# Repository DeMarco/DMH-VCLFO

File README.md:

# DMH-VCLFO
Kosmo format Voltage Controlled tripple LFO module

## Features
6 waveforms, all +5V/-5V
  - Square
  - Saw
  - Ramp
  - Random
  - Sine
  - Triangle

3 frequency ranges
  - Fast
  - Super Fast (Audio rate!)
  - Slow

Hard Sync input

Can also do VCO duties!

Excellent V/Oct trackig over 5 octaves

CV Amount knob serves as Fine Frequency Adjustment when no cable is connected to CV input

Adjustable range for Fine knob

## Current consumption:
+12V --> 65mA

-12V --> 60mA

## Dimensions
Height: 20cm

Width: 10cm

Depth: 10cm

## PCB set
- Panel
- Controls
- Main
- Submodule (x3)

Final Gerbers available in "Gerbers" folder

## Single VCLFO version
The KiCad project named "Single Unit" contains the circuit for one VCLFO in a single page schematic without any inter-PCB connectors. This can be useful if anyone is interested in designing their own PCBs or entire modules in non-Kosmo dimensions.

## Font
For viewing/customizing in KiCad, I recommend downloading and installing the Nulshock font from Typodermic: https://typodermicfonts.com/nulshock/

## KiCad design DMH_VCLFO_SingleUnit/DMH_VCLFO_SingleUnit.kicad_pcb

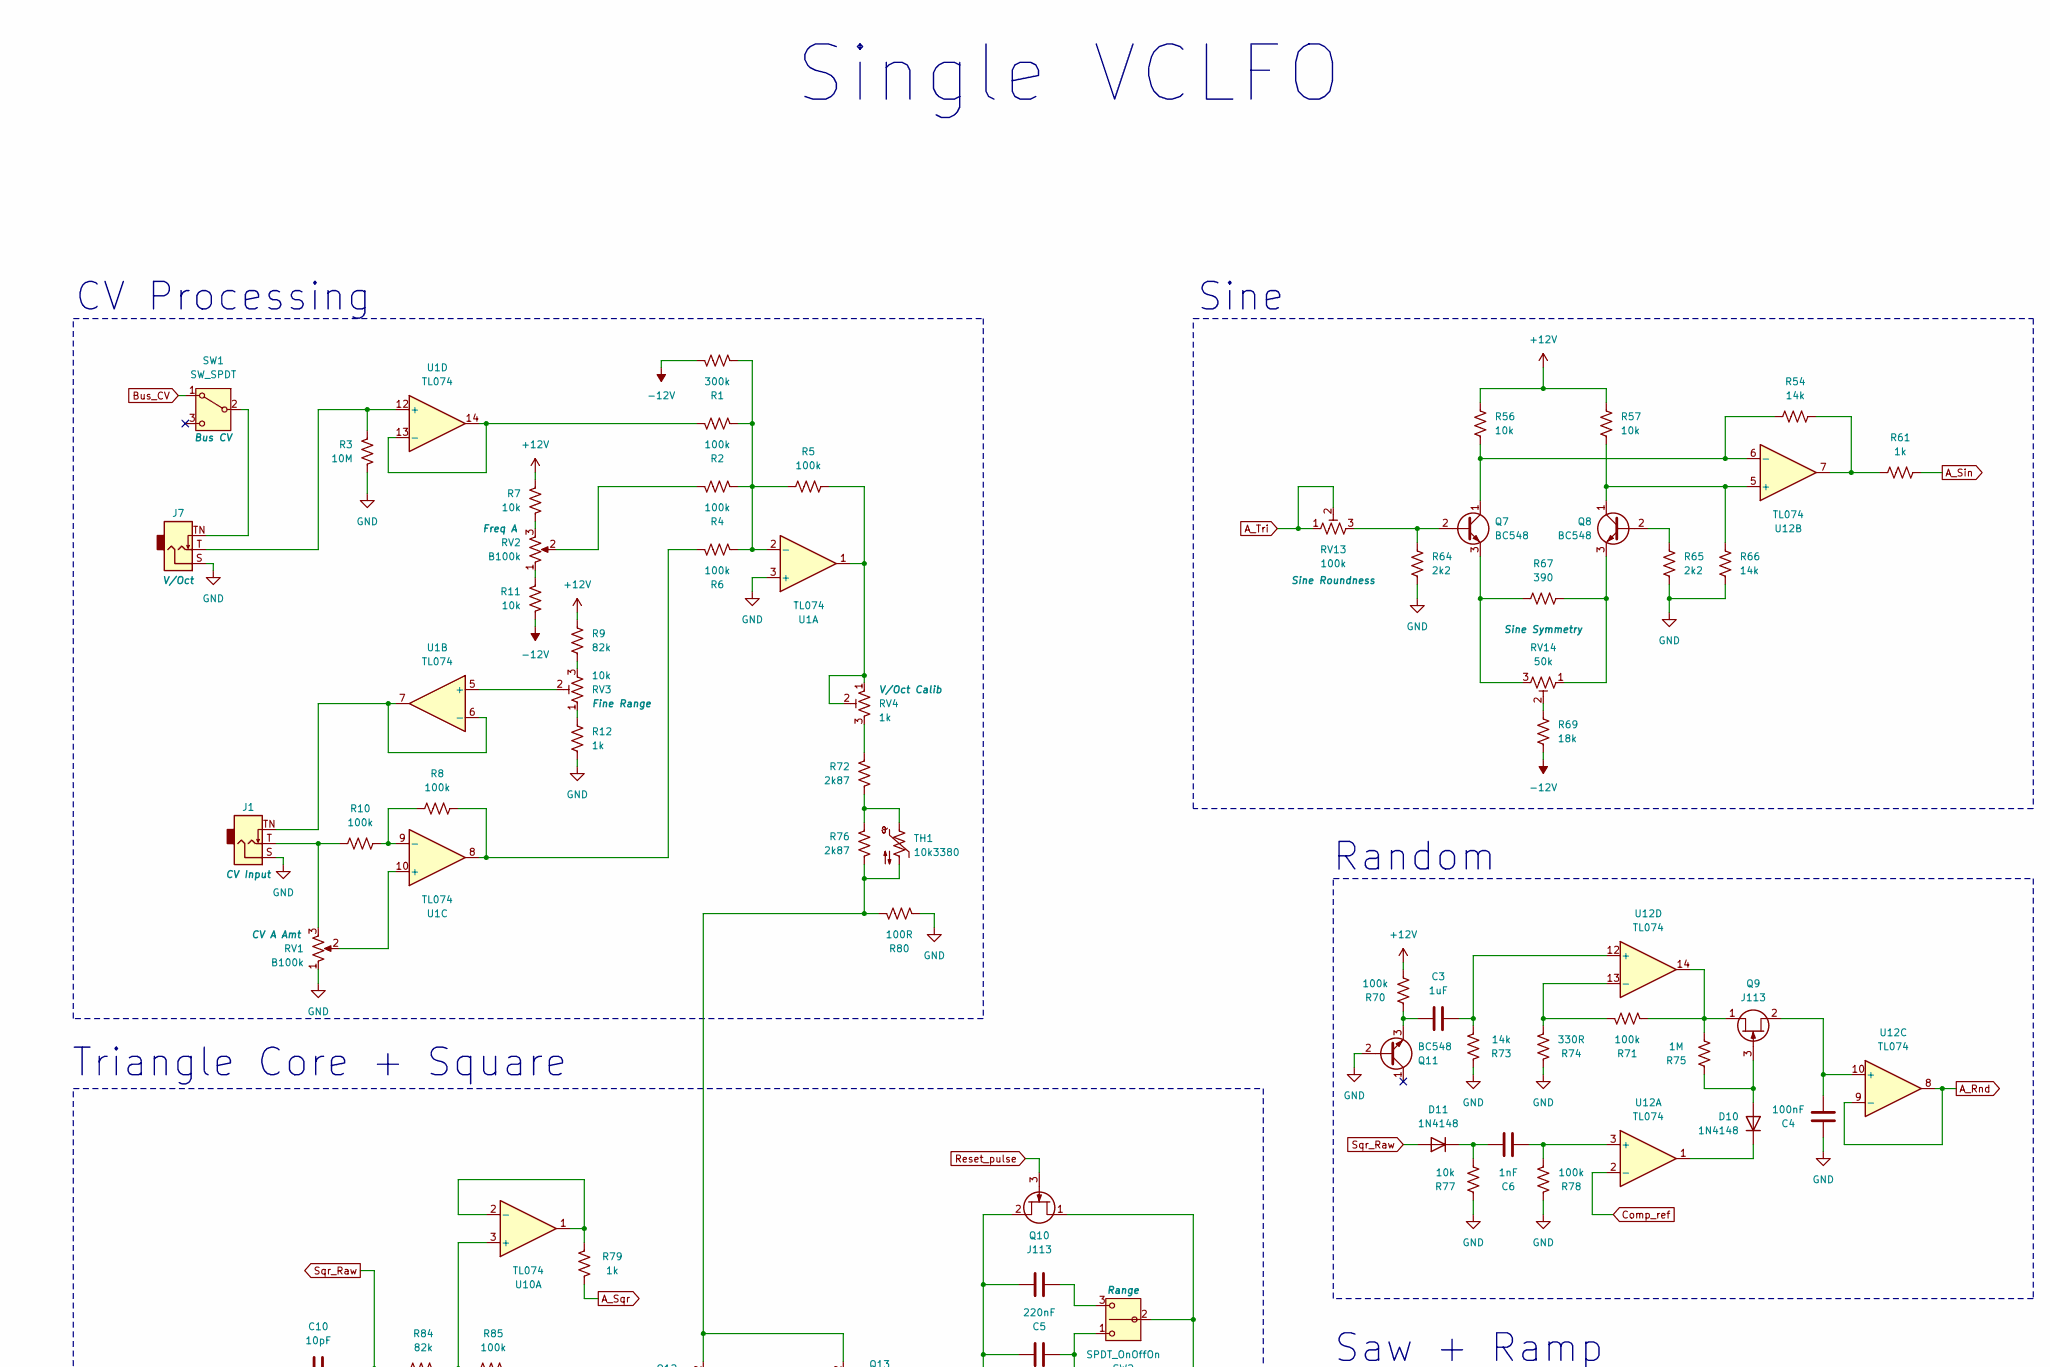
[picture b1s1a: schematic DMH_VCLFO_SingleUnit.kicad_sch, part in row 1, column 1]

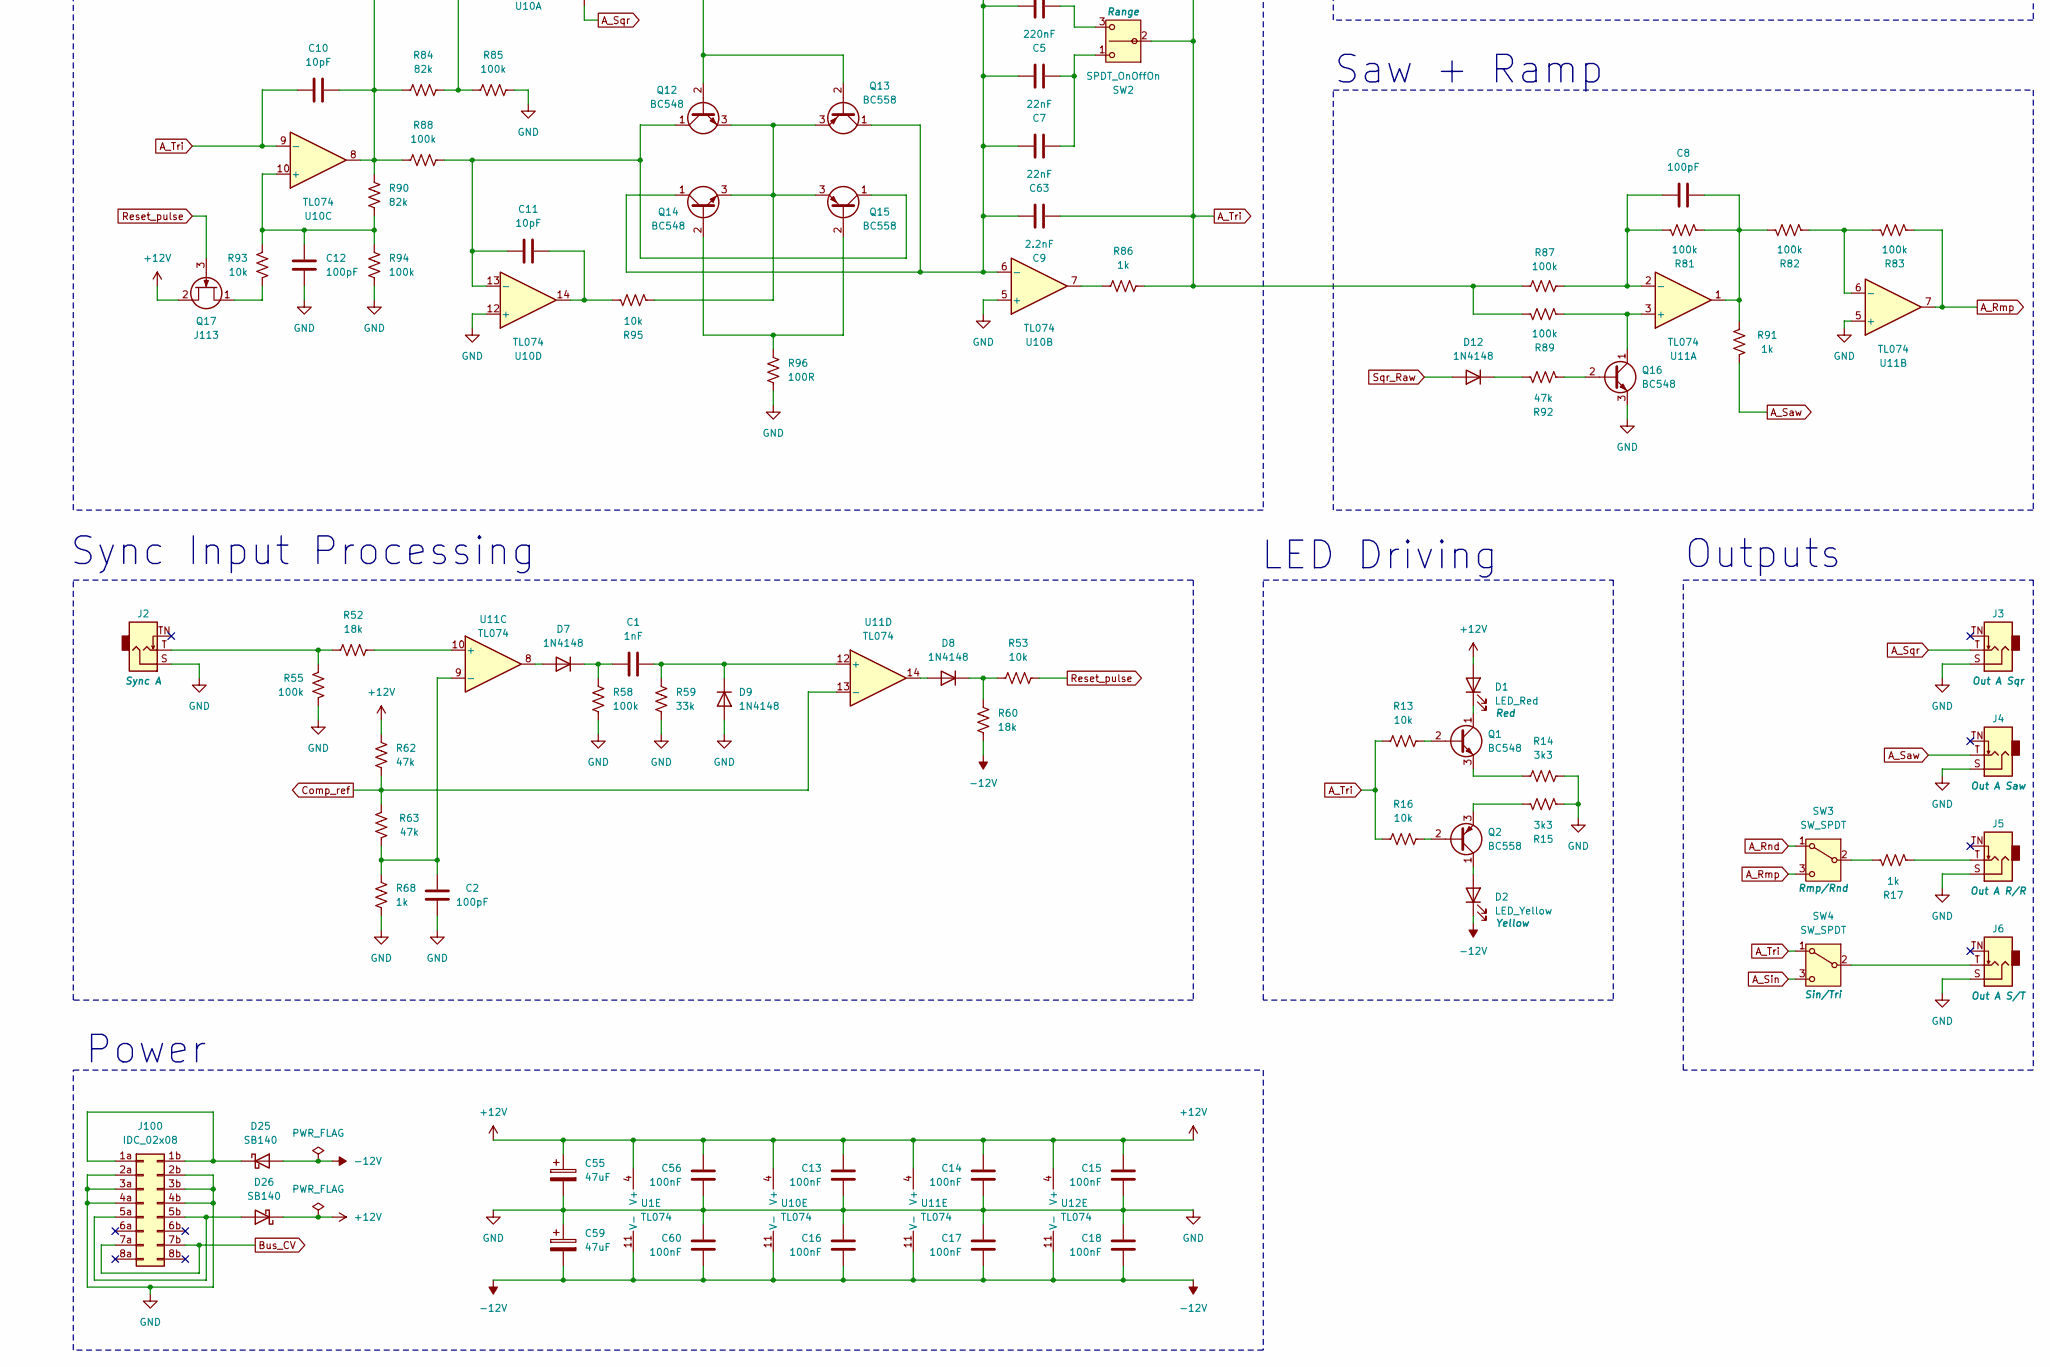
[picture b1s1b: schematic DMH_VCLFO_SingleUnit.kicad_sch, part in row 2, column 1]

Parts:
C1, C6: 1nF; C_Disc_D4.3mm_W1.9mm_P5.00mm
C2, C8, C12: 100pF; C_Disc_D3.0mm_W2.0mm_P2.50mm
C3: 1uF; C_Disc_D4.3mm_W1.9mm_P5.00mm
C4, C13, C14, C15, C16, C17, C18, C56, C60: 100nF; C_Disc_D4.3mm_W1.9mm_P5.00mm
C5: 220nF; C_Disc_D4.3mm_W1.9mm_P5.00mm
C7, C63: 22nF; C_Disc_D4.3mm_W1.9mm_P5.00mm
C9: 2.2nF; C_Disc_D3.0mm_W2.0mm_P2.50mm
C10, C11: 10pF; C_Disc_D3.0mm_W2.0mm_P2.50mm
C55, C59: 47uF; CP_Radial_D5.0mm_P2.00mm
D1: LED_Red; LED_D3.0mm
D2: LED_Yellow; LED_D3.0mm
D7, D8, D9, D10, D11, D12: 1N4148; D_DO-35_SOD27_P7.62mm_Horizontal
D25, D26: SB140; D_DO-41_SOD81_P10.16mm_Horizontal
J1, J2, J3, J4, J5, J6, J7: TS_Jack_6.35mm_Sw; CUI_MJ-63052A
J100: IDC_02x08; IDC-Header_2x08_P2.54mm_Vertical_Eurorack
Q1, Q7, Q8, Q11, Q12, Q14, Q16: BC548; TO-92L_Inline_Wide
Q2, Q13, Q15: BC558; TO-92L_Inline_Wide
Q9, Q10, Q17: J113; TO-92L_Inline
R1: 300k; R_Axial_DIN0207_L6.3mm_D2.5mm_P7.62mm_Horizontal
R2, R4, R5, R6, R8, R10, R55, R58, R70, R71, R78, R81, R82, R83, R85, R87, R88, R89, R94: 100k; R_Axial_DIN0207_L6.3mm_D2.5mm_P7.62mm_Horizontal
R3: 10M; R_Axial_DIN0207_L6.3mm_D2.5mm_P7.62mm_Horizontal
R7, R11, R13, R16, R53, R56, R57, R77, R93, R95: 10k; R_Axial_DIN0207_L6.3mm_D2.5mm_P7.62mm_Horizontal
R9, R84, R90: 82k; R_Axial_DIN0207_L6.3mm_D2.5mm_P7.62mm_Horizontal
R12, R17, R61, R68, R79, R86, R91: 1k; R_Axial_DIN0207_L6.3mm_D2.5mm_P7.62mm_Horizontal
R14, R15: 3k3; R_Axial_DIN0207_L6.3mm_D2.5mm_P7.62mm_Horizontal
R52, R60, R69: 18k; R_Axial_DIN0207_L6.3mm_D2.5mm_P7.62mm_Horizontal
R54, R66, R73: 14k; R_Axial_DIN0207_L6.3mm_D2.5mm_P7.62mm_Horizontal
R59: 33k; R_Axial_DIN0207_L6.3mm_D2.5mm_P7.62mm_Horizontal
R62, R63, R92: 47k; R_Axial_DIN0207_L6.3mm_D2.5mm_P7.62mm_Horizontal
R64, R65: 2k2; R_Axial_DIN0207_L6.3mm_D2.5mm_P7.62mm_Horizontal
R67: 390; R_Axial_DIN0207_L6.3mm_D2.5mm_P7.62mm_Horizontal
R72, R76: 2k87; R_Axial_DIN0207_L6.3mm_D2.5mm_P7.62mm_Horizontal
R74: 330R; R_Axial_DIN0207_L6.3mm_D2.5mm_P7.62mm_Horizontal
R75: 1M; R_Axial_DIN0207_L6.3mm_D2.5mm_P7.62mm_Horizontal
R80, R96: 100R; R_Axial_DIN0207_L6.3mm_D2.5mm_P7.62mm_Horizontal
RV1, RV2: B100k; Potentiometer_Alpha_RD901F-40-00D_Single_Vertical
RV3: 10k; Potentiometer_Bourns_3296W_Vertical
RV4: 1k; Potentiometer_Bourns_3296W_Vertical
RV13: 100k; Potentiometer_Bourns_3296W_Vertical
RV14: 50k; Potentiometer_Bourns_3296W_Vertical
SW1, SW3, SW4: SW_SPDT; Toggle_Switch_TE
SW2: SPDT_OnOffOn; Toggle_Switch_TE
TH1: 10k3380; R_Axial_DIN0204_L3.6mm_D1.6mm_P1.90mm_Vertical
U1, U10, U11, U12: TL074; DIP-14_W7.62mm_Socket

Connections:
+12V: C13.1, C14.1, C15.1, C55.1, C56.1, D1.2 (A), D26.1 (K), Q17.2 (S), R7.1, R9.2, R56.1, R57.1, R62.1, R70.1, U1.4 (V+), U10.4 (V+), U11.4 (V+), U12.4 (V+)
-12V: C16.2, C17.2, C18.2, C59.2, C60.2, D2.1 (K), D25.2 (A), R1.1, R11.2, R60.2, R69.1, U1.11 (V-), U10.11 (V-), U11.11 (V-), U12.11 (V-)
A_Rmp: R83.2, SW3.3 (C), U11.7
A_Rnd: SW3.1 (A), U12.8, U12.9 (-)
A_Saw: J4.T, R91.1
A_Sin: R61.2, SW4.3 (C)
A_Sqr: J3.T, R79.1
A_Tri: C9.2, C10.1, Q10.1 (D), R13.1, R16.1, R86.1, R87.1, R89.1, RV13.1, RV13.2, SW2.2 (B), SW4.1 (A), U10.9 (-)
Bus_CV: J100.7a, J100.7b, SW1.1 (A)
Comp_ref: R62.2, R63.1, U11.13 (-), U12.2 (-)
GND: C2.1, C4.2, C12.1, C13.2, C14.2, C15.2, C16.1, C17.1, C18.1, C55.2, C56.2, C59.1, C60.1, D9.2 (A), J1.S, J2.S, J3.S, J4.S, J5.S, J6.S, J7.S, J100.2a, J100.2b, J100.3a, J100.3b, J100.4a, J100.4b, Q11.2 (B), Q16.3 (E), R3.2, R12.1, R14.2, R15.2, R55.1, R58.2, R59.2, R64.2, R65.2, R66.2, R68.2, R73.2, R74.2, R77.2, R78.2, R80.1, R85.1, R94.2, R96.2, RV1.1, U1.3 (+), U10.5 (+), U10.12 (+), U11.5 (+)
unnamed: C8.2, R81.2, R82.1, R91.2, U11.1
unnamed: C11.2, R95.2, U10.14
unnamed: D1.1 (K), Q1.1 (C)
unnamed: D2.2 (A), Q2.1 (C)
unnamed: D7.2 (A), U11.8
unnamed: C1.1, D7.1 (K), R58.1
unnamed: D8.2 (A), U11.14
unnamed: D8.1 (K), R53.2, R60.1
unnamed: C1.2, D9.1 (K), R59.1, U11.12 (+)
unnamed: D10.2 (A), Q9.3 (G), R75.2
unnamed: D10.1 (K), U12.1
unnamed: C6.2, D11.1 (K), R77.1
unnamed: D12.1 (K), R92.1
unnamed: D25.1 (K), J100.1a, J100.1b
unnamed: D26.2 (A), J100.5a, J100.5b
unnamed: J1.T, R10.1, RV1.3
unnamed: J2.T, R52.1, R55.2
unnamed: J5.T, R17.2
unnamed: Q1.2 (B), R13.2
unnamed: Q1.3 (E), R14.1
unnamed: Q2.2 (B), R16.2
unnamed: Q2.3 (E), R15.1
unnamed: Q7.2 (B), R64.1, RV13.3
unnamed: Q7.1 (C), R54.1, R56.2, U12.6 (-)
unnamed: Q7.3 (E), R67.1, RV14.3
unnamed: Q8.2 (B), R65.1
unnamed: Q8.1 (C), R57.2, R66.1, U12.5 (+)
unnamed: Q8.3 (E), R67.2, RV14.1
unnamed: Q9.1 (D), R71.1, R75.1, U12.14
unnamed: C4.1, Q9.2 (S), U12.10 (+)
unnamed: C5.1, C7.1, C9.1, C63.1, Q10.2 (S), Q13.1 (C), Q14.1 (C), U10.6 (-)
unnamed: C3.1, Q11.3 (E), R70.2
unnamed: Q12.2 (B), Q13.2 (B), R76.2, R80.2, TH1.2
unnamed: C11.1, Q12.1 (C), Q15.1 (C), R88.1, U10.13 (-)
unnamed: Q12.3 (E), Q13.3 (E), Q14.3 (E), Q15.3 (E), R95.1
unnamed: Q14.2 (B), Q15.2 (B), R96.1
unnamed: Q16.2 (B), R92.2
unnamed: Q16.1 (C), R89.2, U11.3 (+)
unnamed: Q17.1 (D), R93.2
unnamed: R4.2, RV2.2
unnamed: R5.2, RV4.1, RV4.2, U1.1
unnamed: R6.2, R8.2, U1.8
unnamed: R7.2, RV2.3
unnamed: R9.1, RV3.3
unnamed: R11.1, RV2.1
unnamed: R12.2, RV3.1
unnamed: R54.2, R61.1, U12.7
unnamed: R69.2, RV14.2
unnamed: R72.1, RV4.3
unnamed: R72.2, R76.1, TH1.1
unnamed: R86.2, U10.7
unnamed: J7.TN, SW1.2 (B)
unnamed: C7.2, C63.2, SW2.1 (A)
unnamed: C5.2, SW2.3 (C)
unnamed: R17.1, SW3.2 (B)
unnamed: J6.T, SW4.2 (B)
unnamed: R1.2, R2.1, R4.1, R5.1, R6.1, U1.2 (-)
unnamed: RV3.2, U1.5 (+)
unnamed: J1.TN, U1.6 (-), U1.7
unnamed: RV1.2, U1.10 (+)
unnamed: R8.1, R10.2, U1.9 (-)
unnamed: J7.T, R3.1, U1.12 (+)
unnamed: R2.2, U1.13 (-), U1.14
unnamed: R84.1, R85.2, U10.3 (+)
unnamed: R79.2, U10.1, U10.2 (-)
unnamed: C12.2, R90.2, R93.1, R94.1, U10.10 (+)
unnamed: C8.1, R81.1, R87.2, U11.2 (-)
unnamed: R82.2, R83.1, U11.6 (-)
unnamed: R52.2, U11.10 (+)
unnamed: C2.2, R63.2, R68.1, U11.9 (-)
unnamed: C6.1, R78.1, U12.3 (+)
unnamed: C3.2, R73.1, U12.12 (+)
unnamed: R71.2, R74.1, U12.13 (-)
Reset_pulse: Q10.3 (G), Q17.3 (G), R53.1
Sqr_Raw: C10.2, D11.2 (A), D12.2 (A), R84.2, R88.2, R90.1, U10.8

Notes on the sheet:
Random
Triangle Core + Square
Sine
CV Processing
Single VCLFO
Outputs
Power
Saw + Ramp
LED Driving
Sync Input Processing

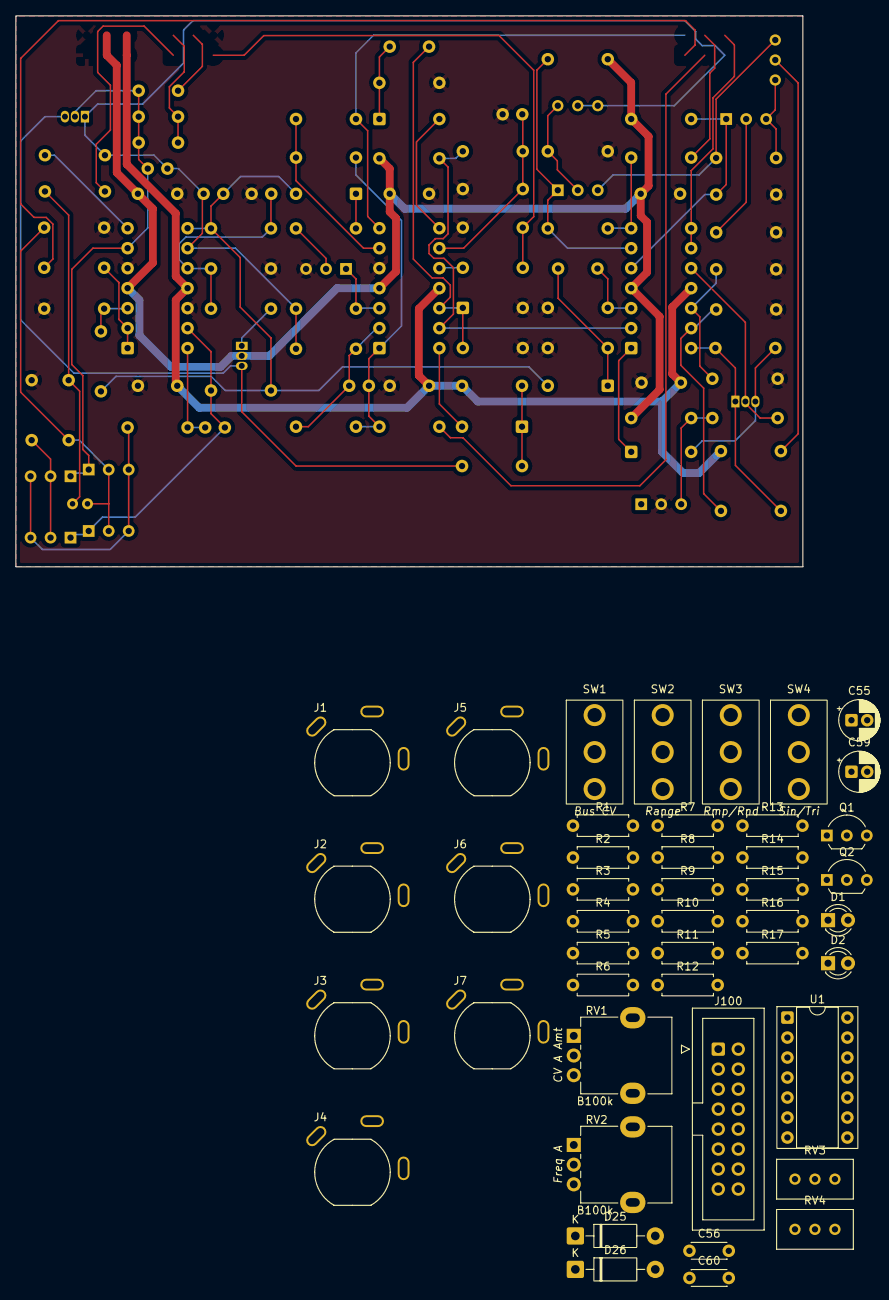
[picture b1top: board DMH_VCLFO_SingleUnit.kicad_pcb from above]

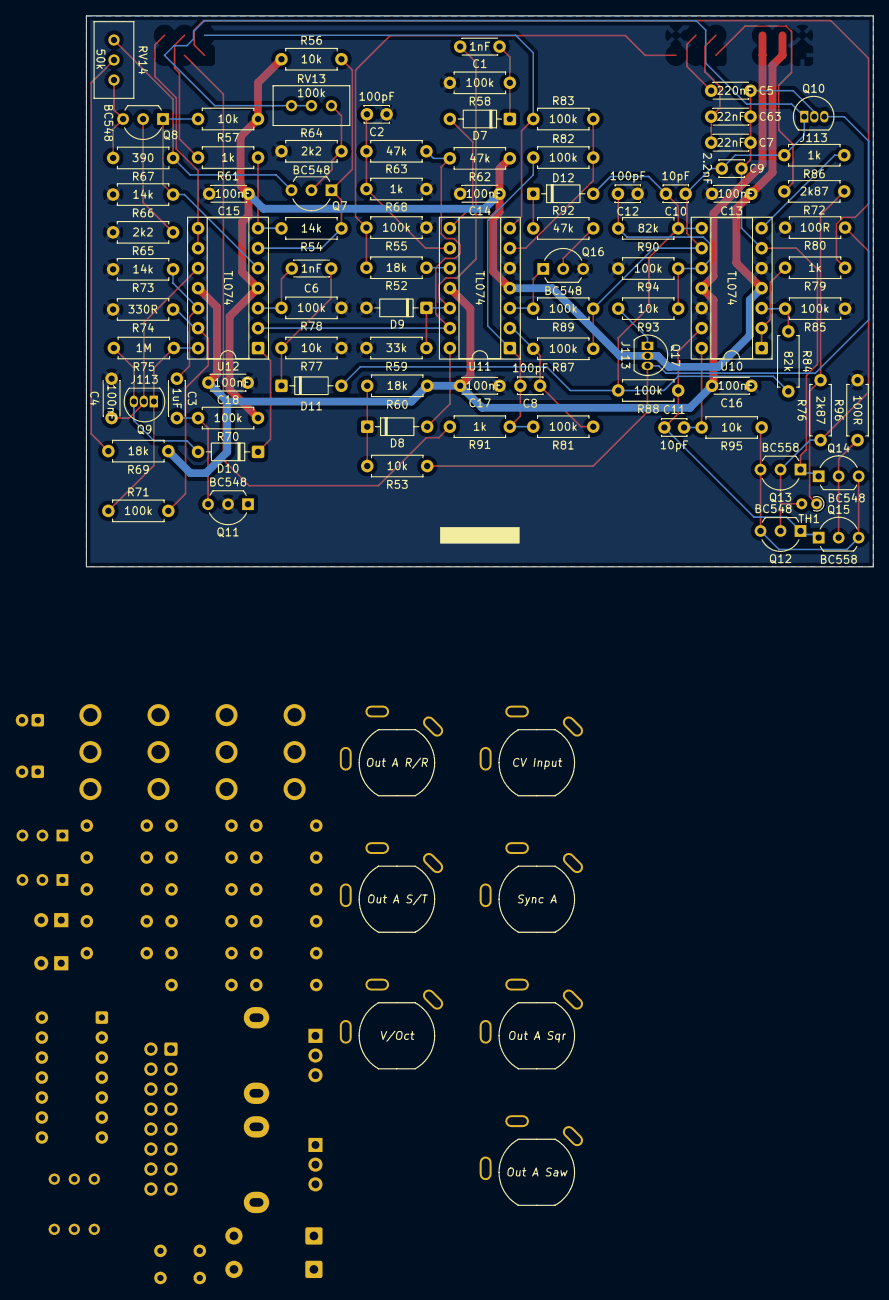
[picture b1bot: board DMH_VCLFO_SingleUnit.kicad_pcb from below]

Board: 2 copper layers, 100.0 x 70.0 mm, 131 parts (87 on the bottom side), 86 nets.

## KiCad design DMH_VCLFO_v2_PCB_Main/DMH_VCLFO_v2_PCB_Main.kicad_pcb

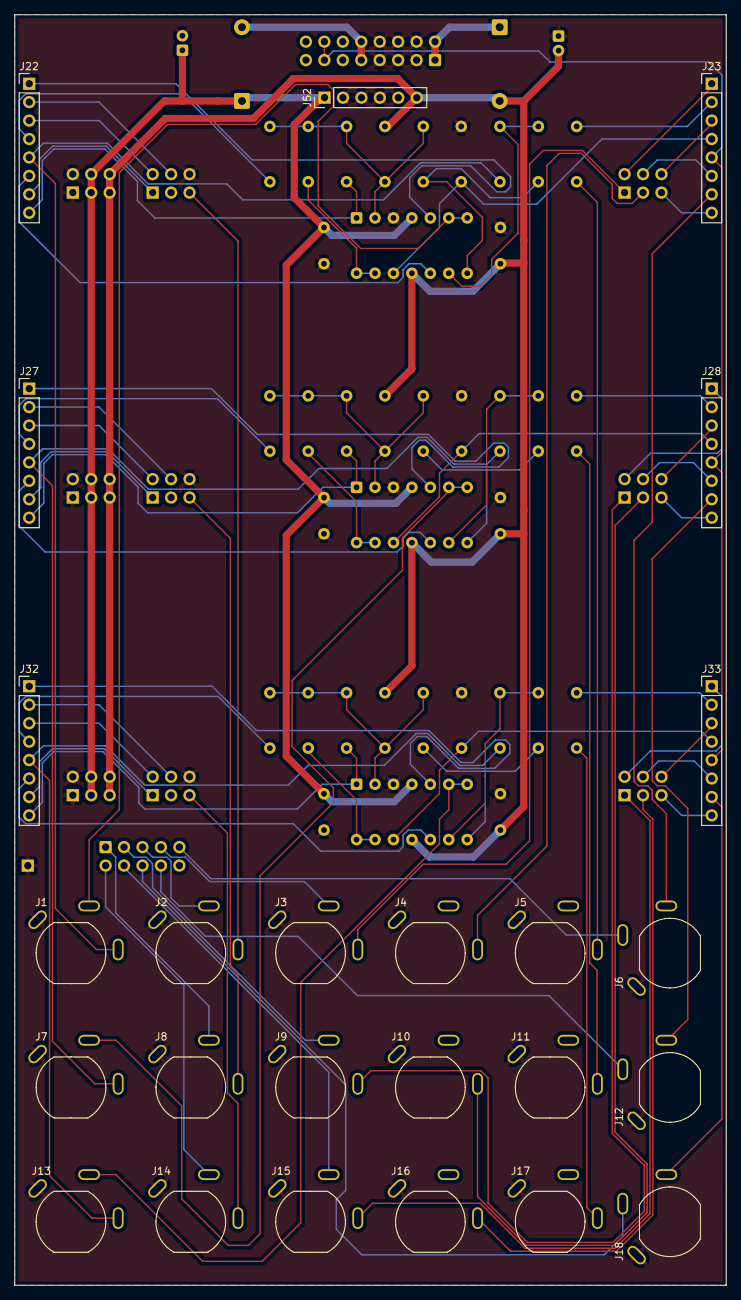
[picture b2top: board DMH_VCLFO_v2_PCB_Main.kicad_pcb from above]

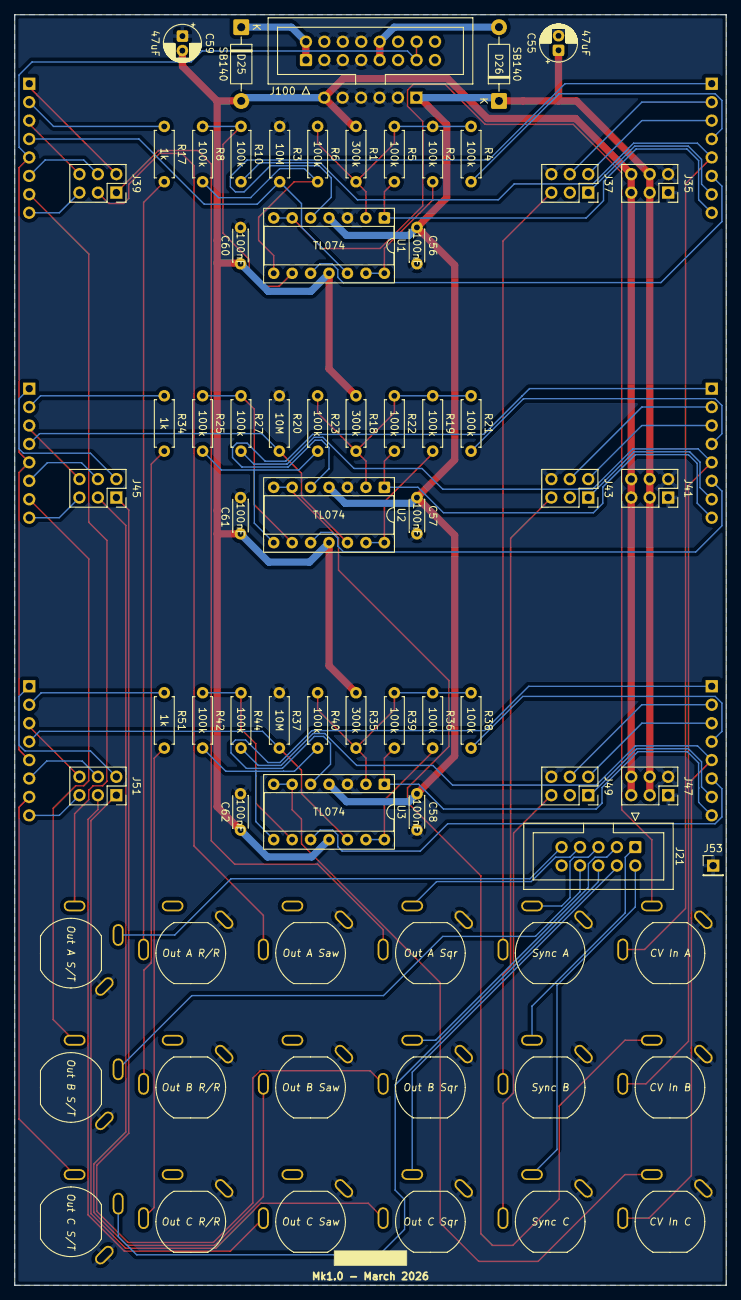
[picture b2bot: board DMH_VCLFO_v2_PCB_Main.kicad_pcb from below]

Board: 2 copper layers, 98.0 x 175.0 mm, 77 parts (52 on the bottom side), 87 nets.

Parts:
C55, C59: 47uF; CP_Radial_D5.0mm_P2.00mm
C56, C57, C58, C60, C61, C62: 100nF; C_Disc_D4.3mm_W1.9mm_P5.00mm
D25, D26: SB140; D_DO-41_SOD81_P10.16mm_Horizontal
J1, J2, J3, J4, J5, J6, J7, J8, J9, J10, J11, J12, J13, J14, J15, J16, J17, J18: TS_Jack_6.35mm_Sw; CUI_MJ-63052A
J21: IDC_02x05; IDC-Header_2x05_P2.54mm_Vertical_BackBone
J22, J23, J27, J28, J32, J33: Conn_01x08; PinHeader_1x08_P2.54mm_Vertical
J35, J37, J39, J41, J43, J45, J47, J49, J51: Conn_02x03_Odd_Even; PinSocket_2x03_P2.54mm_Vertical
J52: Conn_01x06; PinHeader_1x06_P2.54mm_Vertical
J53: Conn_01x01; PinHeader_1x01_P2.54mm_Vertical
J100: IDC_02x08; IDC-Header_2x08_P2.54mm_Vertical_Eurorack
R1, R18, R35: 300k; R_Axial_DIN0207_L6.3mm_D2.5mm_P7.62mm_Horizontal
R2, R4, R5, R6, R8, R10, R19, R21, R22, R23, R25, R27, R36, R38, R39, R40, R42, R44: 100k; R_Axial_DIN0207_L6.3mm_D2.5mm_P7.62mm_Horizontal
R3, R20, R37: 10M; R_Axial_DIN0207_L6.3mm_D2.5mm_P7.62mm_Horizontal
R17, R34, R51: 1k; R_Axial_DIN0207_L6.3mm_D2.5mm_P7.62mm_Horizontal
U1, U2, U3: TL074; DIP-14_W7.62mm_Socket

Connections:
+12V: C55.1, C56.1, C57.1, C58.1, D26.1 (K), J35.3, J35.4, J41.3, J41.4, J47.3, J47.4, J52.1, U1.4 (V+), U2.4 (V+), U3.4 (V+)
-12V: C59.2, C60.2, C61.2, C62.2, D25.2 (A), J35.5, J35.6, J41.5, J41.6, J47.5, J47.6, J52.6, R1.1, R18.1, R35.1, U1.11 (V-), U2.11 (V-), U3.11 (V-)
A_BusCV_Sw_p2_M: J23.4, R3.1, U1.12 (+)
A_CV_Amt_Pot_p2_M: J22.6, U1.10 (+)
A_CV_Amt_Pot_p3_M: J1.T, J22.5, R10.1
A_FRng_Trim_p2_M: J22.1, U1.5 (+)
A_Freq_Pot_p2_M: J22.4, R4.2
A_Out_Sin_Tri_TN_M: J6.TN, J21.5
A_Out_Sqr_TN_M: J3.TN, J21.4
A_Rmp_M: J23.1, J39.2
A_Rmp_Rnd_Sw_p2_M: J23.2, R17.1
A_Rnd_M: J23.3, J39.6
A_Rng_Sw_p1_M: J22.3, J37.2
A_Rng_Sw_p3_M: J22.2, J37.4
A_Saw_M: J4.T, J39.3
A_Sin_M: J23.6, J39.4
A_Sin_Tri_Sw_p2_M: J6.T, J23.7
A_Sqr_M: J3.T, J39.1
A_Sync_M: J2.T, J37.5
A_Sync_TN_M: J2.TN, J21.3
A_Tri_M: J23.8, J39.5
A_VOct_Trim_p3_M: J22.7, J37.1
A_VOct_Trim_p12_M: J22.8, R5.2, U1.1
B_BusCV_Sw_p2_M: J28.4, R20.1, U2.12 (+)
B_CV_Amt_Pot_p2_M: J27.6, U2.10 (+)
B_CV_Amt_Pot_p3_M: J7.T, J27.5, R27.1
B_FRng_Trim_p2_M: J27.1, U2.5 (+)
B_Freq_Pot_p2_M: J27.4, R21.2
B_Out_Sin_Tri_TN_M: J12.TN, J21.9
B_Out_Sqr_TN_M: J9.TN, J21.2
B_Rmp_M: J28.1, J45.2
B_Rmp_Rnd_Sw_p2_M: J28.2, R34.1
B_Rnd_M: J28.3, J45.6
B_Rng_Sw_p1_M: J27.3, J43.2
B_Rng_Sw_p3_M: J27.2, J43.4
B_Saw_M: J10.T, J45.3
B_Sin_M: J28.6, J45.4
B_Sin_Tri_Sw_p2_M: J12.T, J28.7
B_Sqr_M: J9.T, J45.1
B_Sync_M: J8.T, J43.5
B_Sync_TN_M: J8.TN, J21.1
B_Tri_M: J28.8, J45.5
B_VOct_Trim_p3_M: J27.7, J43.1
B_VOct_Trim_p12_M: J27.8, R22.2, U2.1
Bus_CV_M: J23.5, J28.5, J33.5, J100.7a, J100.7b
C_BusCV_Sw_p2_M: J33.4, R37.1, U3.12 (+)
C_CV_Amt_Pot_p2_M: J32.6, U3.10 (+)
C_CV_Amt_Pot_p3_M: J13.T, J32.5, R44.1
C_FRng_Trim_p2_M: J32.1, U3.5 (+)
C_Freq_Pot_p2_M: J32.4, R38.2
C_Out_Sin_Tri_TN_M: J18.TN, J21.8
C_Out_Sqr_TN_M: J15.TN, J21.7
C_Rmp_M: J33.1, J51.2
C_Rmp_Rnd_Sw_p2_M: J33.2, R51.1
C_Rnd_M: J33.3, J51.6
C_Rng_Sw_p1_M: J32.3, J49.2
C_Rng_Sw_p3_M: J32.2, J49.4
C_Saw_M: J16.T, J51.3
C_Sin_M: J33.6, J51.4
C_Sin_Tri_Sw_p2_M: J18.T, J33.7
C_Sqr_M: J15.T, J51.1
C_Sync_M: J14.T, J49.5
C_Sync_TN_M: J14.TN, J21.6
C_Tri_M: J33.8, J51.5
C_VOct_Trim_p3_M: J32.7, J49.1
C_VOct_Trim_p12_M: J32.8, R39.2, U3.1
GND: C55.2, C56.2, C57.2, C58.2, C59.1, C60.1, C61.1, C62.1, J1.S, J2.S, J3.S, J4.S, J5.S, J6.S, J7.S, J8.S, J9.S, J10.S, J11.S, J12.S, J13.S, J14.S, J15.S, J16.S, J17.S, J18.S, J35.1, J35.2, J37.6, J41.1, J41.2, J43.6, J47.1, J47.2, J49.6, J52.2, J52.3, J52.4, J52.5, J53.1, J100.2a, J100.2b, J100.3a, J100.3b, J100.4a, J100.4b, R3.2, R20.2, R37.2, U1.3 (+), U2.3 (+), U3.3 (+)
unnamed: D25.1 (K), J100.1a, J100.1b
unnamed: D26.2 (A), J100.5a, J100.5b
unnamed: J5.T, R17.2
unnamed: J11.T, R34.2
unnamed: J17.T, R51.2
unnamed: R6.2, R8.2, U1.8
unnamed: R23.2, R25.2, U2.8
unnamed: R40.2, R42.2, U3.8
unnamed: R1.2, R2.1, R4.1, R5.1, R6.1, U1.2 (-)
unnamed: J1.TN, U1.6 (-), U1.7
unnamed: R8.1, R10.2, U1.9 (-)
unnamed: R2.2, U1.13 (-), U1.14
unnamed: R18.2, R19.1, R21.1, R22.1, R23.1, U2.2 (-)
unnamed: J7.TN, U2.6 (-), U2.7
unnamed: R25.1, R27.2, U2.9 (-)
unnamed: R19.2, U2.13 (-), U2.14
unnamed: R35.2, R36.1, R38.1, R39.1, R40.1, U3.2 (-)
unnamed: J13.TN, U3.6 (-), U3.7
unnamed: R42.1, R44.2, U3.9 (-)
unnamed: R36.2, U3.13 (-), U3.14

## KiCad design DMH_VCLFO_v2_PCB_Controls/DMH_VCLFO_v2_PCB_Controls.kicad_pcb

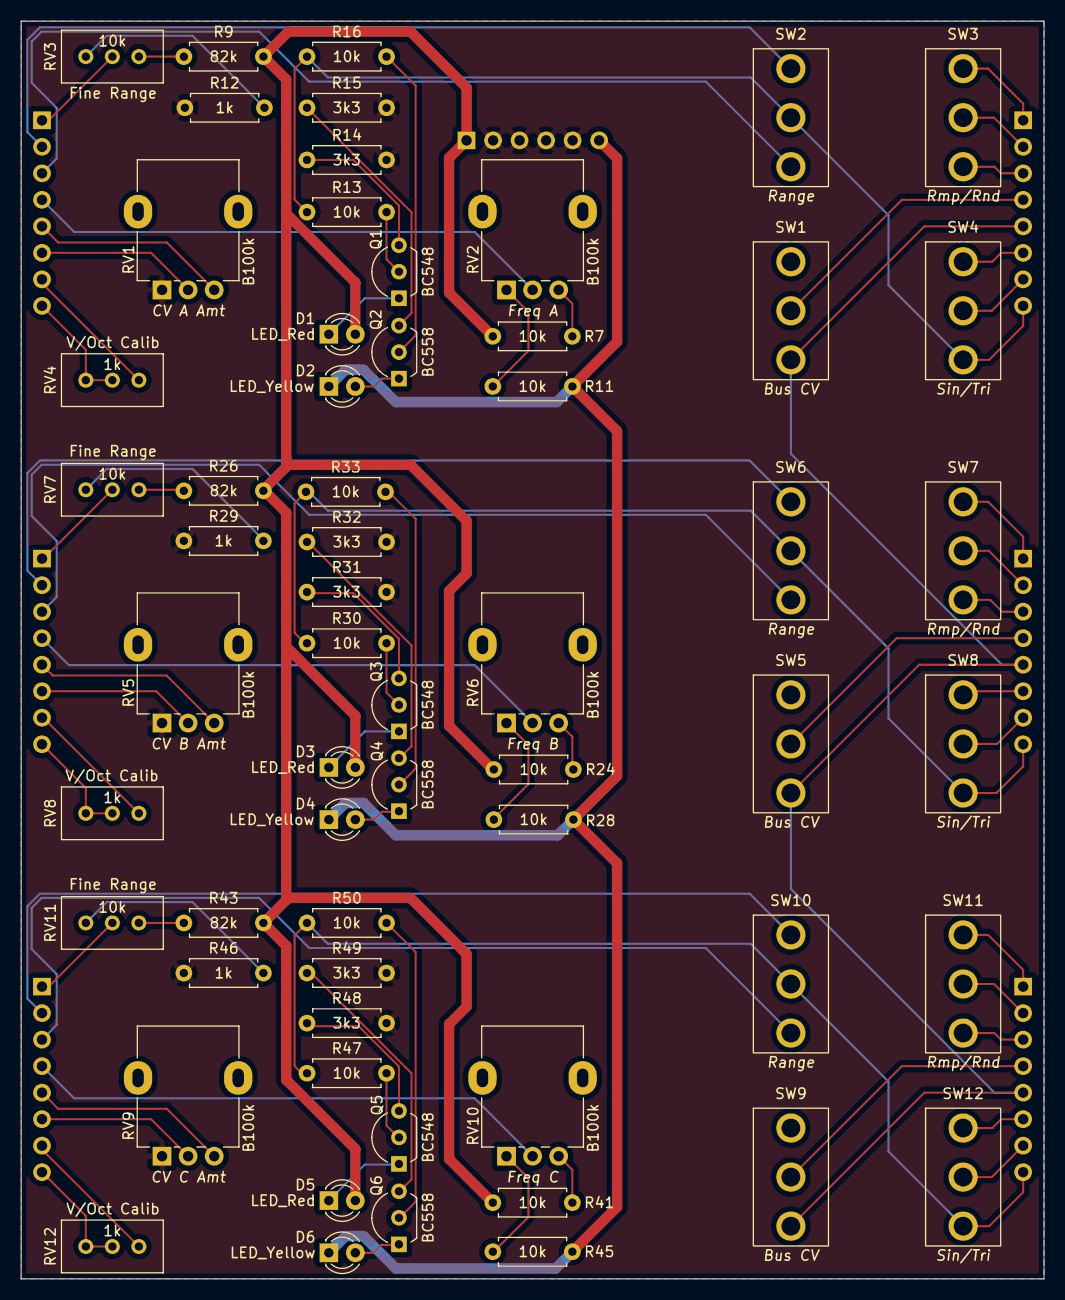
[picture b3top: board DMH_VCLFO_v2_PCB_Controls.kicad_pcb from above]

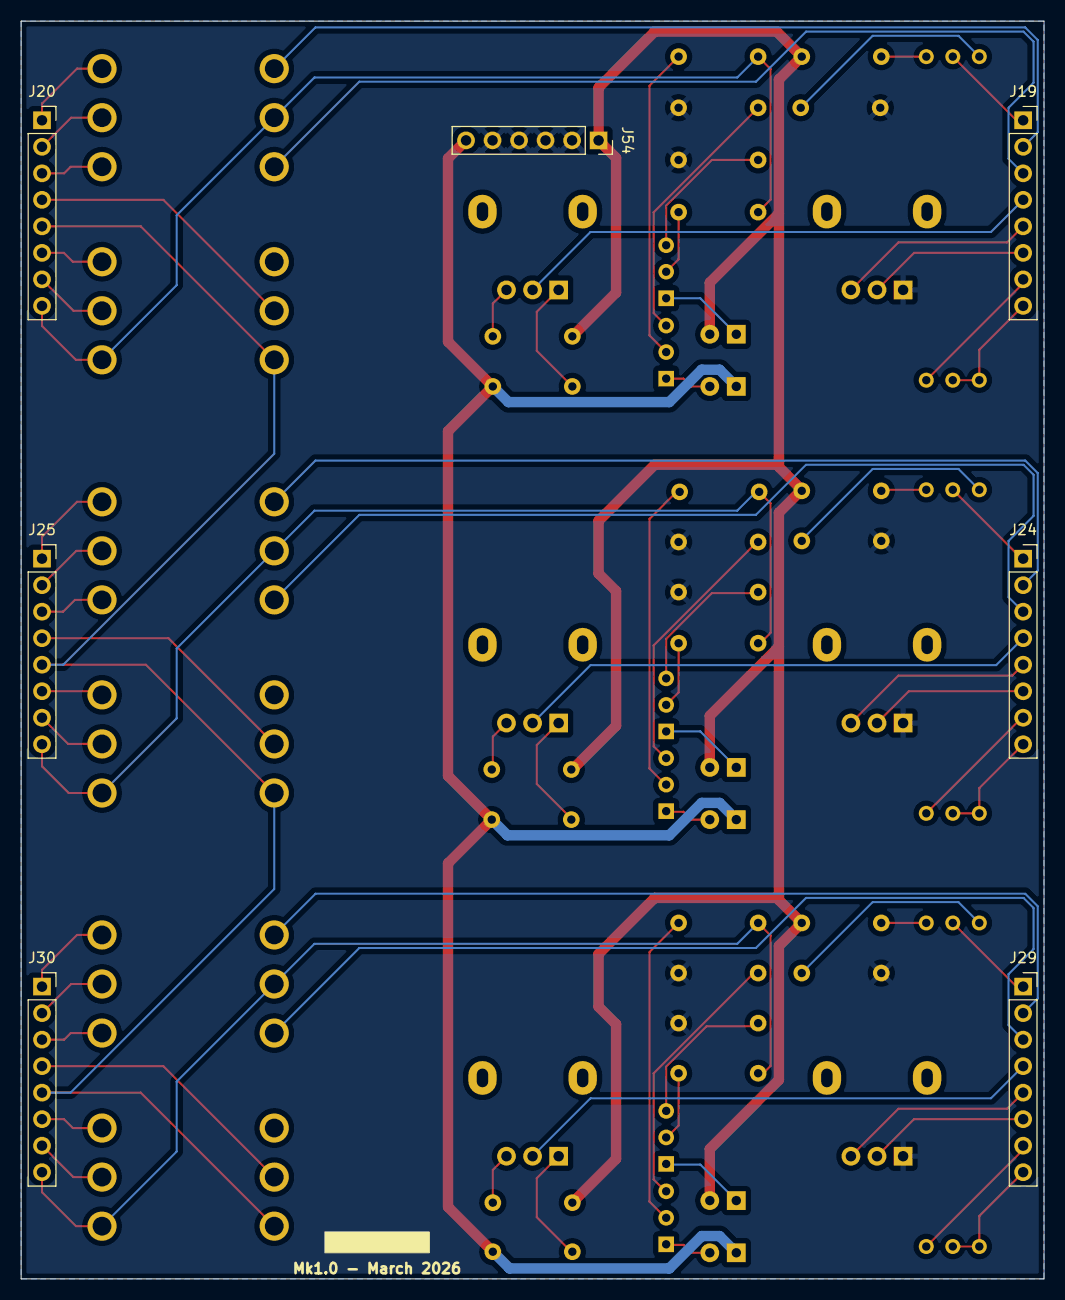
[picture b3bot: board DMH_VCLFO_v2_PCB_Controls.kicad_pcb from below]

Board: 2 copper layers, 98.0 x 120.5 mm, 67 parts (7 on the bottom side), 79 nets.

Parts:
D1, D3, D5: LED_Red; LED_D3.0mm
D2, D4, D6: LED_Yellow; LED_D3.0mm
J19, J20, J24, J25, J29, J30: Conn_01x08; PinSocket_1x08_P2.54mm_Vertical
J54: Conn_01x06; PinSocket_1x06_P2.54mm_Vertical
Q1, Q3, Q5: BC548; TO-92L_Inline_Wide
Q2, Q4, Q6: BC558; TO-92L_Inline_Wide
R7, R11, R13, R16, R24, R28, R30, R33, R41, R45, R47, R50: 10k; R_Axial_DIN0207_L6.3mm_D2.5mm_P7.62mm_Horizontal
R9, R26, R43: 82k; R_Axial_DIN0207_L6.3mm_D2.5mm_P7.62mm_Horizontal
R12, R29, R46: 1k; R_Axial_DIN0207_L6.3mm_D2.5mm_P7.62mm_Horizontal
R14, R15, R31, R32, R48, R49: 3k3; R_Axial_DIN0207_L6.3mm_D2.5mm_P7.62mm_Horizontal
RV1, RV2, RV5, RV6, RV9, RV10: B100k; Potentiometer_Alpha_RD901F-40-00D_Single_Vertical
RV3, RV7, RV11: 10k; Potentiometer_Bourns_3296W_Vertical
RV4, RV8, RV12: 1k; Potentiometer_Bourns_3296W_Vertical
SW1, SW3, SW4, SW5, SW7, SW8, SW9, SW11, SW12: SW_SPDT; Toggle_Switch_TE
SW2, SW6, SW10: SPDT_OnOffOn; Toggle_Switch_TE

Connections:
+12V: D1.2 (A), D3.2 (A), D5.2 (A), J54.1, R7.1, R9.2, R24.1, R26.2, R41.1, R43.2
-12V: D2.1 (K), D4.1 (K), D6.1 (K), J54.6, R11.2, R28.2, R45.2
A_BusCV_Sw_p2_C: J20.4, SW1.2 (B)
A_CV_Amt_Pot_p2_C: J19.6, RV1.2
A_CV_Amt_Pot_p3_C: J19.5, RV1.3
A_FRng_Trim_p2_C: J19.1, RV3.2
A_Freq_Pot_p2_C: J19.4, RV2.2
A_Rmp_C: J20.1, SW3.3 (C)
A_Rmp_Rnd_Sw_p2_C: J20.2, SW3.2 (B)
A_Rnd_C: J20.3, SW3.1 (A)
A_Rng_Sw_p1_C: J19.3, SW2.1 (A)
A_Rng_Sw_p3_C: J19.2, SW2.3 (C)
A_Sin_C: J20.6, SW4.3 (C)
A_Sin_Tri_Sw_p2_C: J20.7, SW4.2 (B)
A_Tri_C: J20.8, R13.1, R16.1, SW2.2 (B), SW4.1 (A)
A_VOct_Trim_p3_C: J19.7, RV4.3
A_VOct_Trim_p12_C: J19.8, RV4.1, RV4.2
B_BusCV_Sw_p2_C: J25.4, SW5.2 (B)
B_CV_Amt_Pot_p2_C: J24.6, RV5.2
B_CV_Amt_Pot_p3_C: J24.5, RV5.3
B_FRng_Trim_p2_C: J24.1, RV7.2
B_Freq_Pot_p2_C: J24.4, RV6.2
B_Rmp_C: J25.1, SW7.3 (C)
B_Rmp_Rnd_Sw_p2_C: J25.2, SW7.2 (B)
B_Rnd_C: J25.3, SW7.1 (A)
B_Rng_Sw_p1_C: J24.3, SW6.1 (A)
B_Rng_Sw_p3_C: J24.2, SW6.3 (C)
B_Sin_C: J25.6, SW8.3 (C)
B_Sin_Tri_Sw_p2_C: J25.7, SW8.2 (B)
B_Tri_C: J25.8, R30.1, R33.1, SW6.2 (B), SW8.1 (A)
B_VOct_Trim_p3_C: J24.7, RV8.3
B_VOct_Trim_p12_C: J24.8, RV8.1, RV8.2
Bus_CV_C: J20.5, J25.5, J30.5, SW1.1 (A), SW5.1 (A), SW9.1 (A)
C_BusCV_Sw_p2_C: J30.4, SW9.2 (B)
C_CV_Amt_Pot_p2_C: J29.6, RV9.2
C_CV_Amt_Pot_p3_C: J29.5, RV9.3
C_FRng_Trim_p2_C: J29.1, RV11.2
C_Freq_Pot_p2_C: J29.4, RV10.2
C_Rmp_C: J30.1, SW11.3 (C)
C_Rmp_Rnd_Sw_p2_C: J30.2, SW11.2 (B)
C_Rnd_C: J30.3, SW11.1 (A)
C_Rng_Sw_p1_C: J29.3, SW10.1 (A)
C_Rng_Sw_p3_C: J29.2, SW10.3 (C)
C_Sin_C: J30.6, SW12.3 (C)
C_Sin_Tri_Sw_p2_C: J30.7, SW12.2 (B)
C_Tri_C: J30.8, R47.1, R50.1, SW10.2 (B), SW12.1 (A)
C_VOct_Trim_p3_C: J29.7, RV12.3
C_VOct_Trim_p12_C: J29.8, RV12.1, RV12.2
GND: J54.2, J54.3, J54.4, J54.5, R12.1, R14.2, R15.2, R29.1, R31.2, R32.2, R46.1, R48.2, R49.2, RV1.1, RV5.1, RV9.1
unnamed: D1.1 (K), Q1.1 (C)
unnamed: D2.2 (A), Q2.1 (C)
unnamed: D3.1 (K), Q3.1 (C)
unnamed: D4.2 (A), Q4.1 (C)
unnamed: D5.1 (K), Q5.1 (C)
unnamed: D6.2 (A), Q6.1 (C)
unnamed: Q1.2 (B), R13.2
unnamed: Q1.3 (E), R14.1
unnamed: Q2.2 (B), R16.2
unnamed: Q2.3 (E), R15.1
unnamed: Q3.2 (B), R30.2
unnamed: Q3.3 (E), R31.1
unnamed: Q4.2 (B), R33.2
unnamed: Q4.3 (E), R32.1
unnamed: Q5.2 (B), R47.2
unnamed: Q5.3 (E), R48.1
unnamed: Q6.2 (B), R50.2
unnamed: Q6.3 (E), R49.1
unnamed: R7.2, RV2.3
unnamed: R9.1, RV3.3
unnamed: R11.1, RV2.1
unnamed: R12.2, RV3.1
unnamed: R24.2, RV6.3
unnamed: R26.1, RV7.3
unnamed: R28.1, RV6.1
unnamed: R29.2, RV7.1
unnamed: R41.2, RV10.3
unnamed: R43.1, RV11.3
unnamed: R45.1, RV10.1
unnamed: R46.2, RV11.1

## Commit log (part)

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2025-04-26 Created Panel project
2025-04-26 V1 one the panel ready
2025-04-26 V2 panel ready
    - Removed attenuverter
    - Re-added saw output
    - Added sync input
    - Added PLL switch
    - Added unipolar switch
2025-04-28 Starting redesign of panel
2025-04-29 Finished panel v3
    Grouped all outputs at the bottom of the module to avoid cables getting in the way of the knobs
2025-10-06 Improved ergonomics
2025-10-20 Replaced PLL with Range
2025-10-20 Added yellow LED to Panel
2025-11-23 Created PCB 1 project
2025-11-26 schematic design in progress
2025-11-30 Completed basic core circuit schematic
    ... escept for polarization switch
2025-11-30 Ready for breadboarding
2025-12-01 Fixed issue with polarity selector
2025-12-06 Sync Libs
2025-12-20 Improved sync input
2025-12-20 Exported preliminary BoM
2026-01-10 Changed name in panel
2026-01-10 Documented breadboard layout
2026-01-12 Annotations during breabboarding troubleshooting
2026-01-13 simulated oscillator core
2026-01-15 Centralized library location
2026-01-24 Breadboard troubleshooting changes
2026-01-24 Synced lib
2026-01-25 Added super fast range option
2026-01-25 Updated fonts on panel
2026-01-29 Preparing schematic for new core circuit
2026-01-31 Designed osc core based on slew module
2026-02-01 Adapted sync reset circuit
2026-02-01 Adapted saw shaper
2026-02-04 Replaced sine shaper and adapted random
2026-02-05 Improved inter-PCB connections
2026-02-08 Notes from breadboarding
2026-02-09 Created lfo core sim 2
2026-02-10 Modified front panel
    Added V/Oct calib trimpot hole
    Replaced Polarity switch with Bus CV
    Added Fine as normalized function of CV Amt pot
2026-02-11 Sch redesign in progress
2026-02-12 Redesigned schematic for V/Oct
    And also Bus CV and Fine tune
2026-02-13 Rearranged symbols in IO page
2026-02-14 Adjustments on breadboard
2026-02-14 Rearranged IO page
2026-02-14 Prepared for PCB design
2026-02-15 Controls PCB comp placement in progress
2026-02-16 Controls PCB routing done
2026-02-18 Main PCB comp placement in progress
2026-02-19 Main PCB placement done
2026-02-19 Routing attempt
2026-02-19 Alternative Main PCB placement ongoing
2026-02-20 Placement attempt done
2026-02-20 Routing in progress
2026-02-21 Main PCB routing done
2026-02-21 Synced Controls PCB with Main
2026-02-21 Created Submodule project
2026-02-21 Submodule comp placement started
2026-02-21 Submodule com placement done
2026-02-21 Submodule routing done
2026-02-21 Generated Gerbers
2026-03-31 Update SynthStuff
2026-04-05 Reorganized folder contents
2026-04-13 Added project with Single VCLFO schematic
2026-04-13 Update README regarding Single Unit version
